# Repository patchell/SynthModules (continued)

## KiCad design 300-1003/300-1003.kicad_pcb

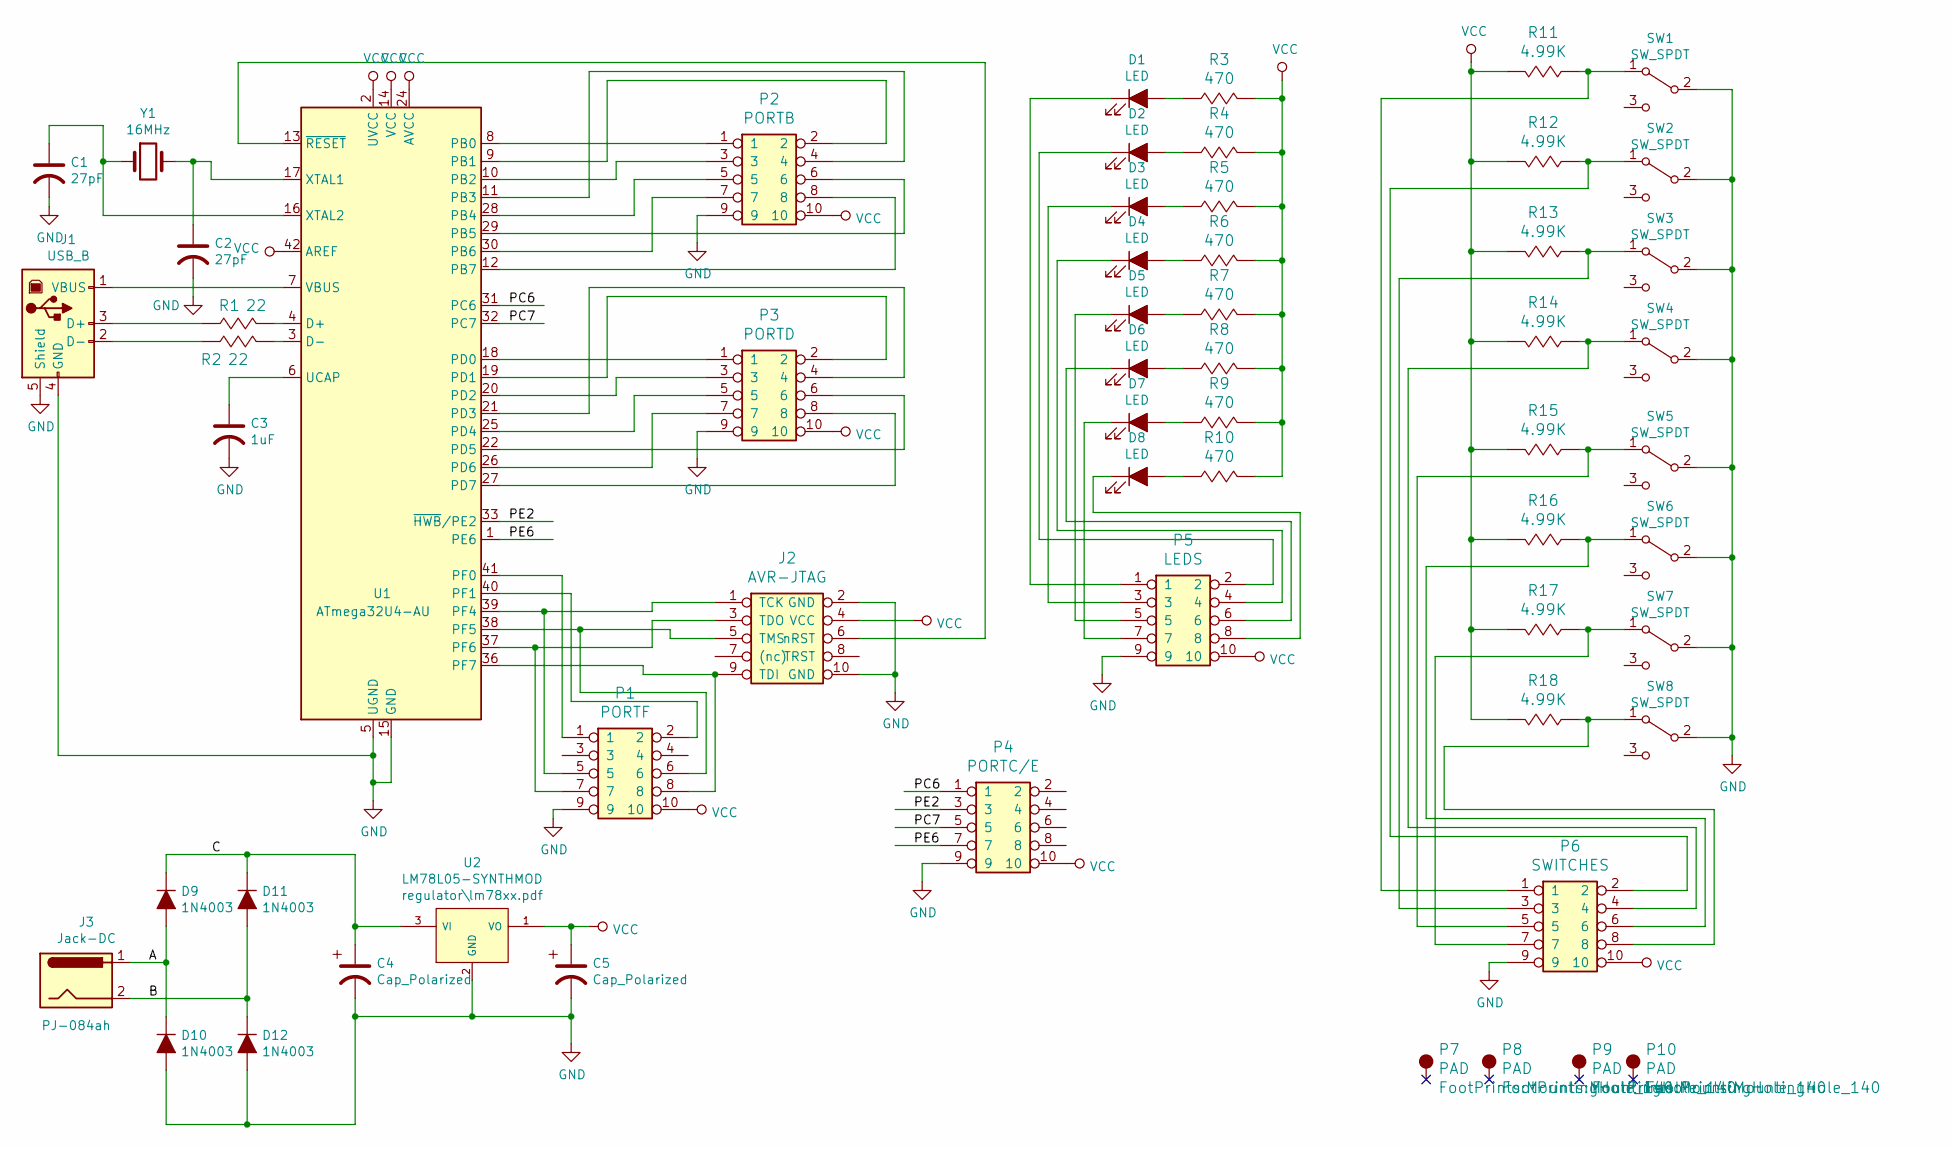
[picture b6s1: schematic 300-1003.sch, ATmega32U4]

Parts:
C1, C2: 27pF; CAP-0.1
C3: 1uF; CAP-GREENIE-0_2
C4, C5: Cap_Polarized; Cap-Pol-Rad-0.2_0.1
D1, D2, D3, D4, D5, D6, D7, D8: LED; LED_5.0mm
D9, D10, D11, D12: 1N4003; DIODE0.4
J1: USB_B
J2: AVR-JTAG; IDC5x2_Vert
J3: Jack-DC; DC-JACK-CUI-PJ-085AH
P1: PORTF; IDC5x2_Vert
P2: PORTB; IDC5x2_Vert
P3: PORTD; IDC5x2_Vert
P4: PORTC/E; IDC5x2_Vert
P5: LEDS; IDC5x2_Vert
P6: SWITCHES; IDC5x2_Vert
P7, P8, P9, P10: PAD; MountingHole_140
R1, R2: 22; AXIAL0_4
R3, R4, R5, R6, R7, R8, R9, R10: 470; AXIAL0_4
R11, R12, R13, R14, R15, R16, R17, R18: 4.99K; AXIAL0_4
SW1, SW2, SW3, SW4, SW5, SW6, SW7, SW8: SW_SPDT; SWITCH_SPDT-OS102011MS2QN1
U1: ATmega32U4-AU; TQFP-44_10x10mm_Pitch0.8mm
U2: LM78L05-SYNTHMOD; TO92
Y1: 16MHz; XTAL

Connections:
/A: D9.2 (A), D10.1 (K), J3.1
/B: D11.2 (A), D12.1 (K), J3.2
/C: C4.1, D9.1 (K), D11.1 (K), U2.3 (VI)
/PC6: P4.1, U1.31 (PC6)
/PC7: P4.5, U1.32 (PC7)
/PE2: P4.3, U1.33 (~HWB~/PE2)
/PE6: P4.7, U1.1 (PE6)
GND: C1.2, C2.2, C3.2, C4.2, C5.2, D10.2 (A), D12.2 (A), J1.4 (GND), J1.5 (Shield), J2.2 (GND), J2.10 (GND), P1.9, P2.9, P3.9, P4.9, P5.9, P6.9, SW1.2 (B), SW2.2 (B), SW3.2 (B), SW4.2 (B), SW5.2 (B), SW6.2 (B), SW7.2 (B), SW8.2 (B), U1.5 (UGND), U1.15 (GND), U1.23 (GND), U1.35 (GND), U1.43 (GND), U2.2 (GND)
unnamed: C1.1, U1.16 (XTAL2), Y1.1
unnamed: C2.1, U1.17 (XTAL1), Y1.2
unnamed: C3.1, U1.6 (UCAP)
unnamed: D1.1 (K), P5.1
unnamed: D1.2 (A), R3.1 (A)
unnamed: D2.1 (K), P5.2
unnamed: D2.2 (A), R4.1 (A)
unnamed: D3.1 (K), P5.3
unnamed: D3.2 (A), R5.1 (A)
unnamed: D4.1 (K), P5.4
unnamed: D4.2 (A), R6.1 (A)
unnamed: D5.1 (K), P5.5
unnamed: D5.2 (A), R7.1 (A)
unnamed: D6.1 (K), P5.6
unnamed: D6.2 (A), R8.1 (A)
unnamed: D7.1 (K), P5.7
unnamed: D7.2 (A), R9.1 (A)
unnamed: D8.1 (K), P5.8
unnamed: D8.2 (A), R10.1 (A)
unnamed: J1.1 (VBUS), U1.7 (VBUS)
unnamed: J1.2 (D-), R2.1 (A)
unnamed: J1.3 (D+), R1.1 (A)
unnamed: J2.1 (TCK), P1.5, U1.39 (PF4)
unnamed: J2.3 (TDO), P1.7, U1.37 (PF6)
unnamed: J2.5 (TMS), P1.6, U1.38 (PF5)
unnamed: J2.6 (nRST), U1.13 (~RESET)
unnamed: J2.9 (TDI), P1.8, U1.36 (PF7)
unnamed: P1.1, U1.41 (PF0)
unnamed: P1.2, U1.40 (PF1)
unnamed: P2.1, U1.8 (PB0)
unnamed: P2.2, U1.9 (PB1)
unnamed: P2.3, U1.10 (PB2)
unnamed: P2.4, U1.11 (PB3)
unnamed: P2.5, U1.28 (PB4)
unnamed: P2.6, U1.29 (PB5)
unnamed: P2.7, U1.30 (PB6)
unnamed: P2.8, U1.12 (PB7)
unnamed: P3.1, U1.18 (PD0)
unnamed: P3.2, U1.19 (PD1)
unnamed: P3.3, U1.20 (PD2)
unnamed: P3.4, U1.21 (PD3)
unnamed: P3.5, U1.25 (PD4)
unnamed: P3.6, U1.22 (PD5)
unnamed: P3.7, U1.26 (PD6)
unnamed: P3.8, U1.27 (PD7)
unnamed: P6.1, R11.1 (A), SW1.1 (A)
unnamed: P6.2, R12.1 (A), SW2.1 (A)
unnamed: P6.3, R13.1 (A), SW3.1 (A)
unnamed: P6.4, R14.1 (A), SW4.1 (A)
unnamed: P6.5, R15.1 (A), SW5.1 (A)
unnamed: P6.6, R16.1 (A), SW6.1 (A)
unnamed: P6.7, R17.1 (A), SW7.1 (A)
unnamed: P6.8, R18.1 (A), SW8.1 (A)
unnamed: R1.2 (B), U1.4 (D+)
unnamed: R2.2 (B), U1.3 (D-)
VCC: C5.1, J2.4 (VCC), P1.10, P2.10, P3.10, P4.10, P5.10, P6.10, R3.2 (B), R4.2 (B), R5.2 (B), R6.2 (B), R7.2 (B), R8.2 (B), R9.2 (B), R10.2 (B), R11.2 (B), R12.2 (B), R13.2 (B), R14.2 (B), R15.2 (B), R16.2 (B), R17.2 (B), R18.2 (B), U1.2 (UVCC), U1.14 (VCC), U1.24 (AVCC), U1.34 (VCC), U1.42 (AREF), U1.44 (AVCC), U2.1 (VO)

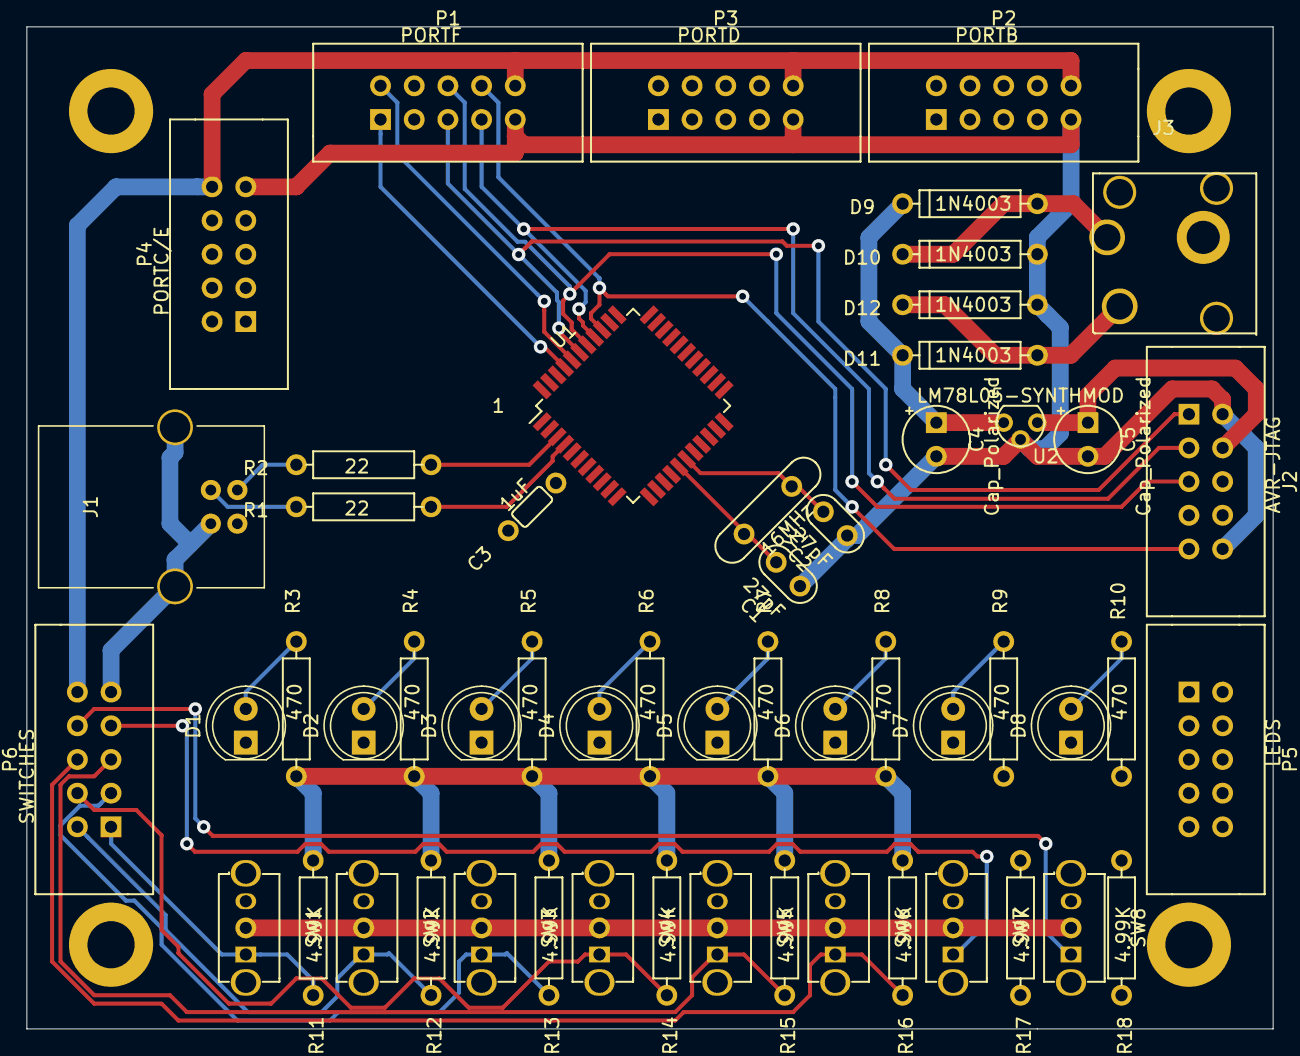
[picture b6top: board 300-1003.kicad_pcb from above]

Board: 2 copper layers, 94.0 x 75.6 mm, 59 parts (0 on the bottom side), 64 nets.
